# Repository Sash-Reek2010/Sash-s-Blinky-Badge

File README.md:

# Sash-s-Blinky-Badge
It's a 555 LED Chaser board (aka a Blinky!) and you can pin it to your clothes and show it off to your friends! It's also shaped like PACMAN!!!
### PCB View

## Components
- NE55p
- CD4017
- Electrolytic Capacitor
- Capacitor
- 1 ohm resistor
- 470 ohm resistor
- Potentiometer
- 10x LEDs

Thanks for reading!!!

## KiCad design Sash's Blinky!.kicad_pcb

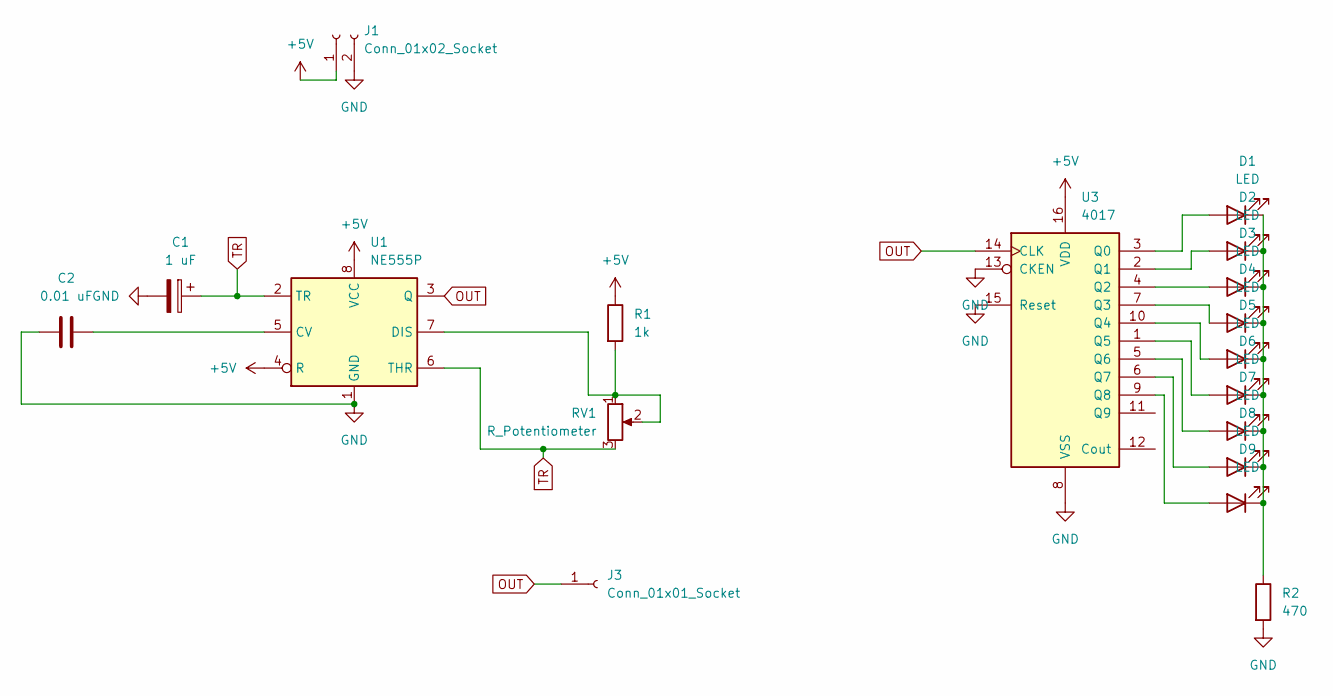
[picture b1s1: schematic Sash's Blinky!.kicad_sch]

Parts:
C1: 1 uF; CP_Radial_D5.0mm_P2.00mm
C2: 0.01 uF; C_Disc_D7.5mm_W2.5mm_P5.00mm
D1, D2, D3, D4, D5, D6, D7, D8, D9: LED; LED_D3.0mm
J1: Conn_01x02_Socket; PinHeader_1x02_P2.54mm_Vertical
J3: Conn_01x01_Socket; PinHeader_1x01_P2.54mm_Vertical
R1: 1k; R_Axial_DIN0207_L6.3mm_D2.5mm_P7.62mm_Horizontal
R2: 470; R_Axial_DIN0207_L6.3mm_D2.5mm_P7.62mm_Horizontal
RV1: R_Potentiometer; Potentiometer_Vishay_T93YA_Vertical
U1: NE555P; DIP-8_W7.62mm
U3: 4017; N16

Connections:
+5V: J1.1, R1.1, U1.4 (R), U1.8 (VCC), U3.16 (VDD)
GND: C1.2, C2.2, J1.2, R2.2, U1.1 (GND), U3.8 (VSS), U3.13 (CKEN), U3.15 (Reset)
unnamed: D1.2 (A), U3.3 (Q0)
unnamed: D1.1 (K), D2.1 (K), D3.1 (K), D4.1 (K), D5.1 (K), D6.1 (K), D7.1 (K), D8.1 (K), D9.1 (K), R2.1
unnamed: D2.2 (A), U3.2 (Q1)
unnamed: D3.2 (A), U3.4 (Q2)
unnamed: D4.2 (A), U3.7 (Q3)
unnamed: D5.2 (A), U3.10 (Q4)
unnamed: D6.2 (A), U3.1 (Q5)
unnamed: D7.2 (A), U3.5 (Q6)
unnamed: D8.2 (A), U3.6 (Q7)
unnamed: D9.2 (A), U3.9 (Q8)
unnamed: C2.1, U1.5 (CV)
unnamed: R1.2, RV1.1, RV1.2, U1.7 (DIS)
OUT: J3.1, U1.3 (Q), U3.14 (CLK)
TR: C1.1, RV1.3, U1.2 (TR), U1.6 (THR)

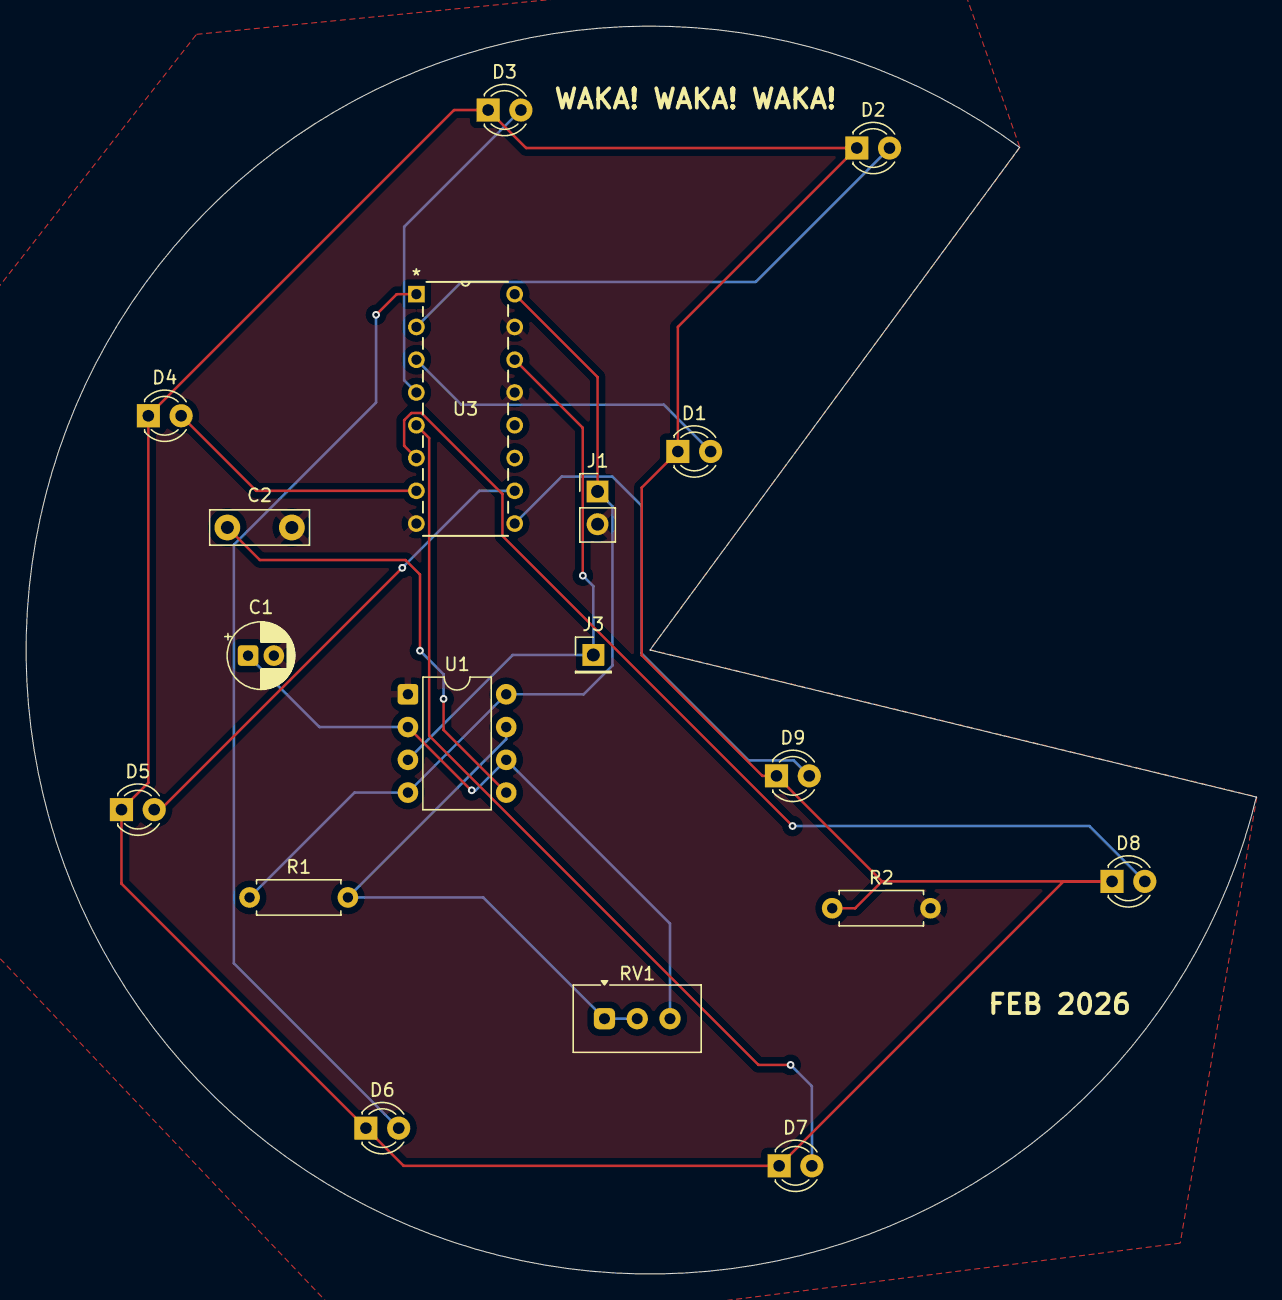
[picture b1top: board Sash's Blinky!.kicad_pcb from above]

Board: 2 copper layers, 95.4 x 96.7 mm, 18 parts (0 on the bottom side), 16 nets.

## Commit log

2026-02-18 Add Files
